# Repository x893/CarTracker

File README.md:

CarTracker
==========

CarTracker
STM32F10xCx, STM32F10xRx, STM32F205Rx, STM32F405Rx, STM32L1xxCx, STM32L1xxRx support.
Telit SL868 or SL869
Telit GL865 or GL868
CAN support,
MMA7455 accelerometer,
standard SIM or SIM On Chip
64 pins version can use battery, USB and RFM70 module (or other)

Shared PCB on OSH Park:

Cx version http://oshpark.com/shared_projects/hou07XOD

Rx version http://oshpark.com/shared_projects/wFTza6Pe

Cx version support direct connection GPS to GSM via wires (or change layout) so you can use buildin Python to implement tracker functions without STM32 MCU.

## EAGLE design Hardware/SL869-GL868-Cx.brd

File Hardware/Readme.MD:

Eagle Cadsoft
Case http://www.gainta.com/en/g431.html
See info for R9 value and R13

Shared PCB on OSH Park:

Cx version http://oshpark.com/shared_projects/hou07XOD
Rx version http://oshpark.com/shared_projects/wFTza6Pe

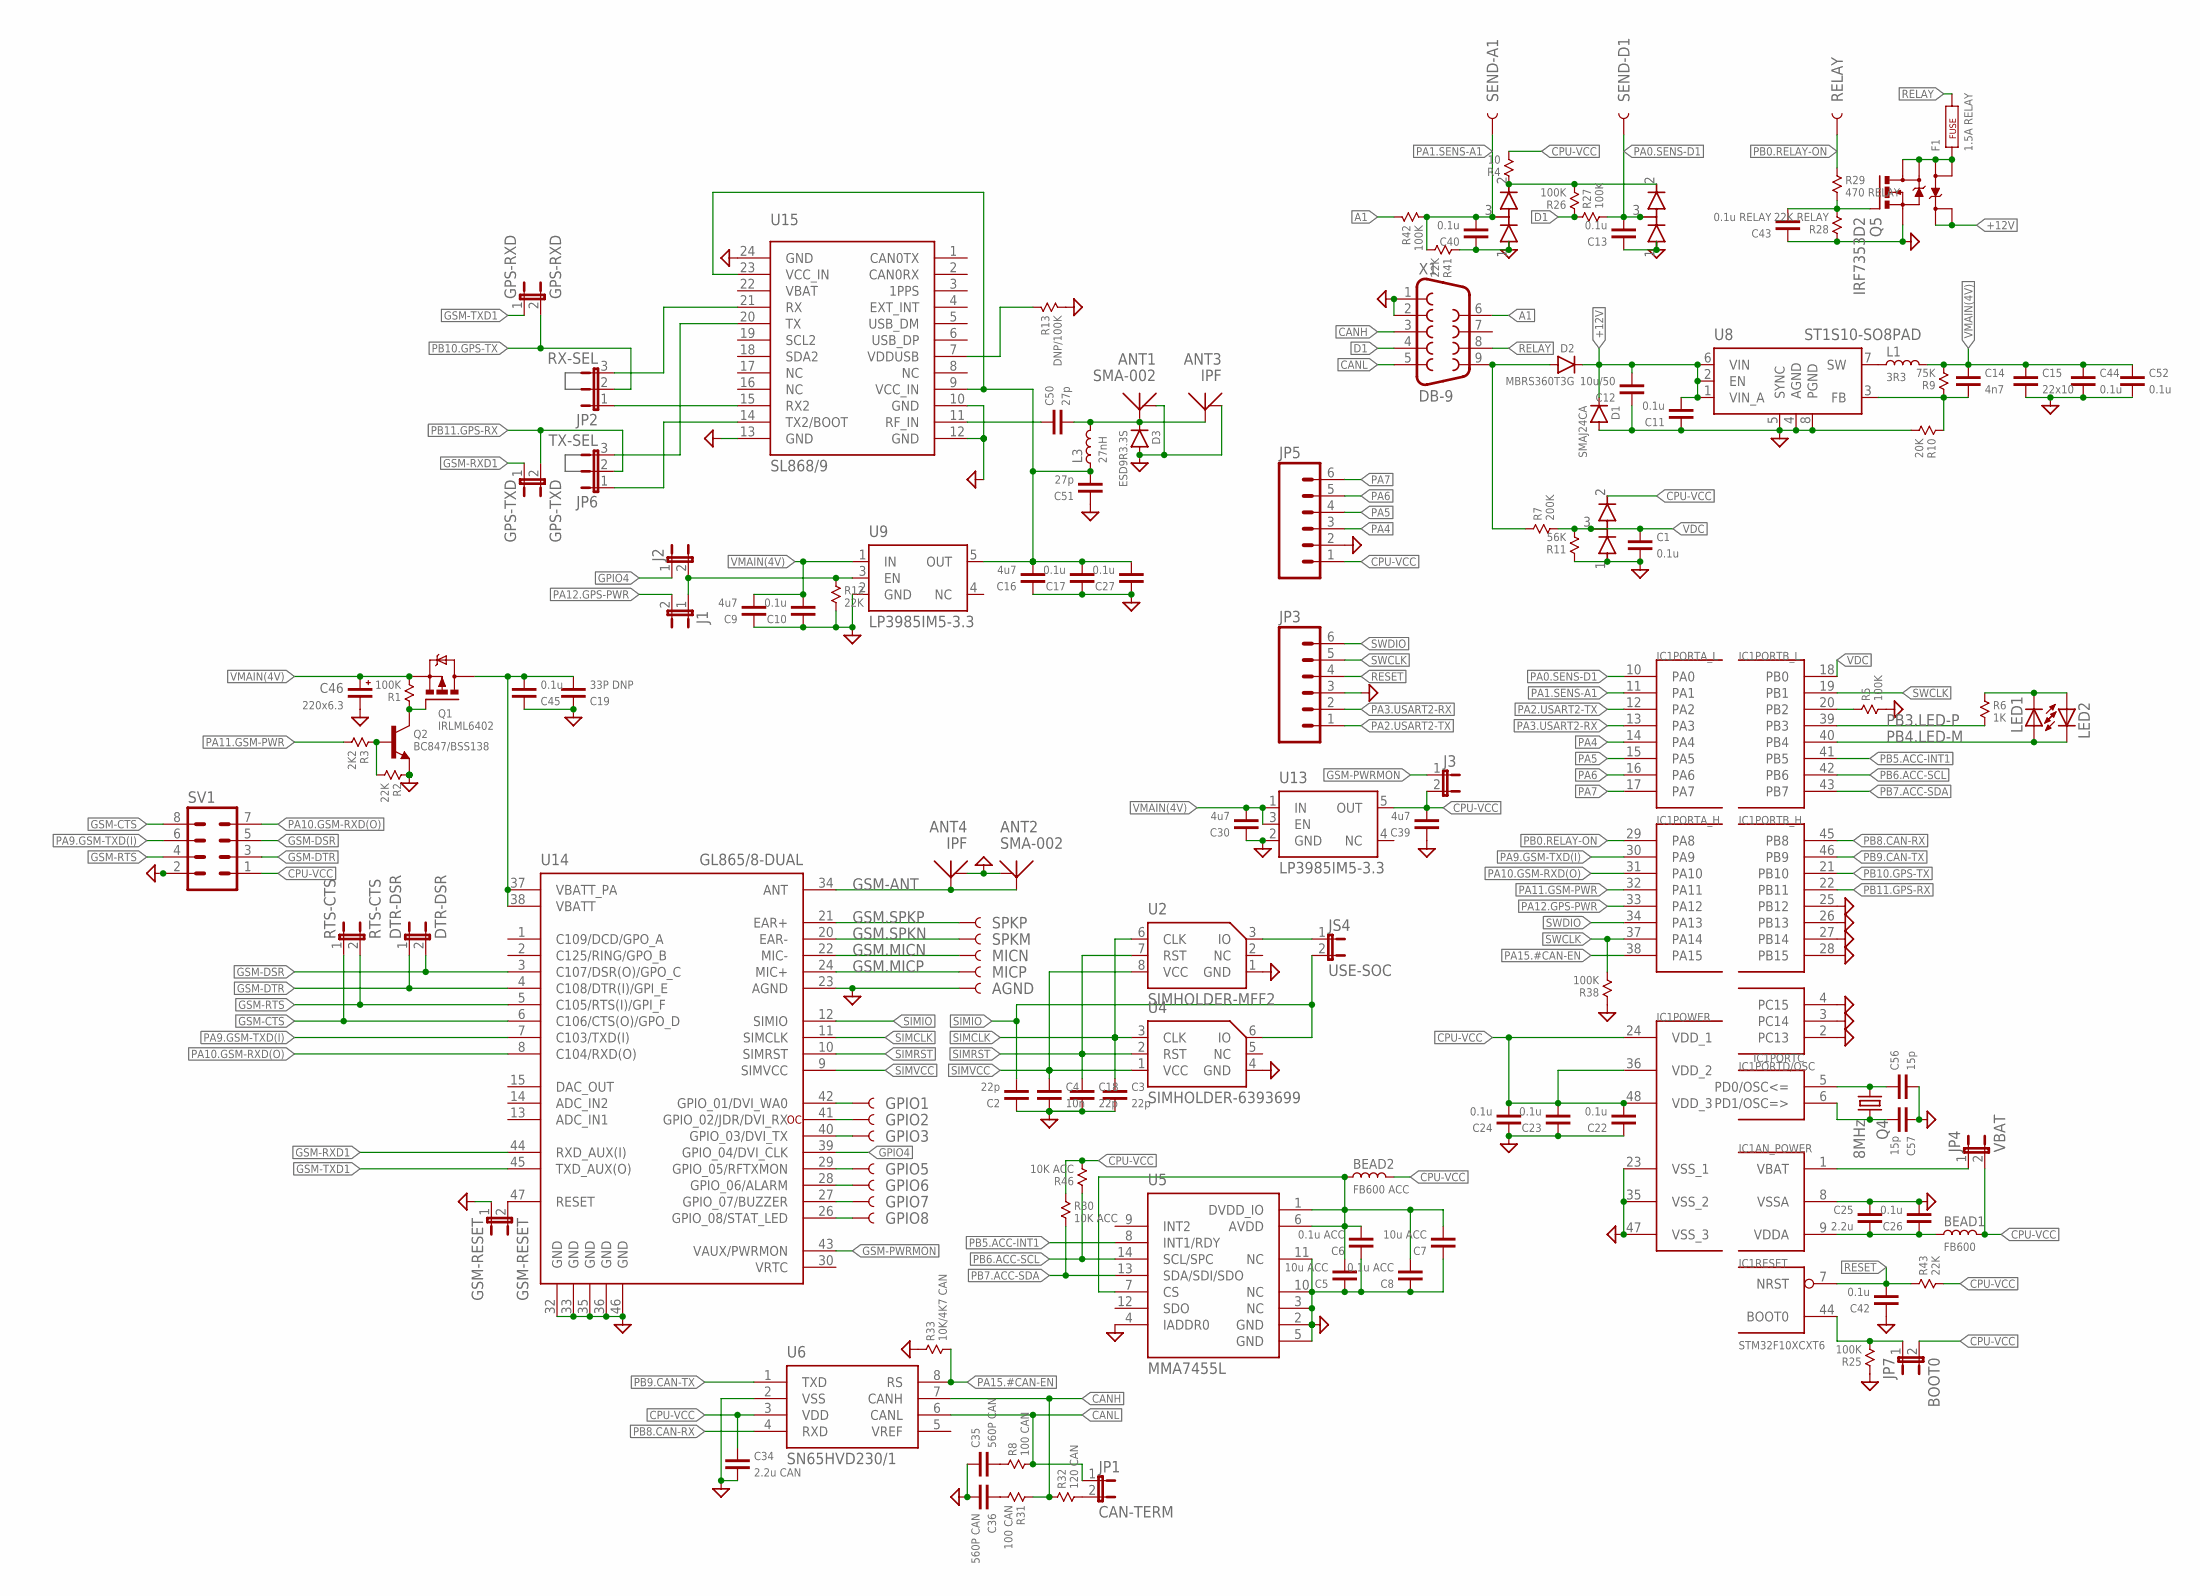
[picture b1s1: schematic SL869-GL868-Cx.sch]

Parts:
AGND: TEST-POINT1; PAD.1X1
ANT1, ANT2: SMA-002
ANT3, ANT4: IPF; MM9329
BEAD1: FB600; 0603
BEAD2: FB600 ACC; 0603
C1, C10, C11, C13, C17, C22, C23, C24, C26, C27, C40, C42, C44, C45, C52: 0.1u; 0603
C2, C3, C18: 22p; 0603
C4: 10n; 0603
C5, C7: 10u ACC; 0603
C6, C8: 0.1u ACC; 0603
C9, C16, C30, C39: 4u7; 0603
C12: 10u/50; 1206
C14: 4n7; 0603
C15: 22x10; 1206
C19: 33P DNP; 0603
C25: 2.2u; 0603
C34: 2.2u CAN; 0603
C35, C36: 560P CAN; 0603
C43: 0.1u RELAY; 0603
C46: 220x6.3; CT7343
C50, C51: 27p; 0603
C56, C57: 15p; 0603
D1: SMAJ24CA; SMA
D2: MBRS360T3G; SMC
D3: ESD9R3.3S; SOD-923
D4, D5, D14: BAV99; SOT-23
DTR-DSR: DTR-DSR; SJ_2S-NO
F1: 1.5A RELAY; 1812
GPIO1, GPIO2, GPIO3, GPIO5, GPIO6, GPIO7, GPIO8: TEST-POINT1; PAD.1X1
GPS-RXD: GPS-RXD; SJ_2S-NO
GPS-TXD: GPS-TXD; SJ_2S-NO
GSM-RESET: GSM-RESET; SJ_2S-NO
IC1: STM32F10XCXT6; TQFP48
J1, J2, J3: JUMPER-2SMD-NO; SJ_2S-NO
JP1: CAN-TERM; SJ_2S-NO
JP2: RX-SEL; SJ_3
JP3, JP5: M06SIP; 1X06
JP4: VBAT; SJ_2S-NO
JP6: TX-SEL; SJ_3
JP7: BOOT0; SJ_2S-NO
JS4: USE-SOC; SJ_2S-NO
L1: 3R3; CDRH6D38NP
L3: 27nH; 0603
LED1, LED2: LED3MM
MICN: TEST-POINT1; PAD.1X1
MICP: TEST-POINT1; PAD.1X1
Q1: IRLML6402; SOT-23
Q2: BC847/BSS138; SOT-23
Q4: 8MHz; HC49U-V
Q5: IRF7353D2; SO08
R1, R5, R25, R26, R27, R38, R42: 100K; 0603
R2, R12, R41, R43: 22K; 0603
R3: 2K2; 0603
R4: 10; 0603
R6: 1K; 0603
R7: 200K; 0603
R8, R31: 100 CAN; 0603
R9: 75K; 0603
R10: 20K; 0603
R11: 56K; 0603
R13: DNP/100K; 0603
R28: 22K RELAY; 0603
R29: 470 RELAY; 0603
R30, R46: 10K ACC; 0603
R32: 120 CAN; 0603
R33: 10K/4K7 CAN; 0603
RELAY: TEST-POINT1; PAD.1X1
RTS-CTS: RTS-CTS; SJ_2S-NO
SEND-A1: TEST-POINT1; PAD.1X1
SEND-D1: TEST-POINT1; PAD.1X1
SPKM: TEST-POINT1; PAD.1X1
SPKP: TEST-POINT1; PAD.1X1
SV1: MA04-2
U2: SIMHOLDER-MFF2; MFF2
U4: SIMHOLDER-6393699; 6393699-1
U5: MMA7455L; LGA14
U6: SN65HVD230/1; SO08
U8: ST1S10-SO8PAD; SO08-EPAD
U9, U13: LP3985IM5-3.3; SOT23-5
U14: GL865/8-DUAL
U15: SL868/9
X1: DB-9; DB9

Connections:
+12-IN: D2.P$2 (A), R7.1, X1.9
+12V: C11.1, C12.1, D1.P$1 (C), D2.P$1 (C), Q5.7 (K), Q5.8 (K), U8.1 (VIN_A), U8.2 (EN), U8.6 (VIN)
A1: R42.1, X1.6
ACC-VCC: BEAD2.1, C5.1, C6.1, C7.1, C8.1, U5.1 (DVDD_IO), U5.6 (AVDD), U5.7 (CS)
CANH: R31.1, R32.1, U6.7 (CANH), X1.3
CANL: JP1.1, R8.2, U6.6 (CANL), X1.5
CPU-VBAT: IC1.1 (VBAT), JP4.1
CPU-VCC: BEAD1.2, BEAD2.2, C22.1, C23.1, C24.1, C34.2, C39.1, D5.2 (+), IC1.24 (VDD_1), IC1.36 (VDD_2), IC1.48 (VDD_3), J3.2, JP4.2, JP5.1, JP7.2, R4.2, R30.1, R43.2, R46.2, SV1.1, U6.3 (VDD), U13.5 (OUT)
D1: R26.1, R27.1, X1.4
GND: AGND.P$1, ANT1.GND@1 (GND), ANT2.GND@1 (GND), ANT3.2 (GND), ANT4.2 (GND), C1.1, C2.2, C3.1, C4.1, C5.2, C6.2, C7.2, C8.2, C9.2, C10.2, C11.2, C12.2, C13.2, C15.1, C16.2, C17.2, C18.1, C19.2, C22.2, C23.2, C24.2, C25.2, C26.1, C27.2, C30.2, C34.1, C35.2, C36.1, C39.2, C40.2, C42.2, C43.2, C44.1, C45.2, C46.-, C51.2, C52.1, C56.1, C57.2, D1.P$2 (A), D3.2 (A), D4.1 (-), D5.1 (-), D14.1 (-), GSM-RESET.1, IC1.2 (PC13), IC1.3 (PC14), IC1.4 (PC15), IC1.8 (VSSA), IC1.23 (VSS_1), IC1.25 (PB12), IC1.26 (PB13), IC1.27 (PB14), IC1.28 (PB15), IC1.35 (VSS_2), IC1.47 (VSS_3), JP3.3, JP5.2, Q2.2 (E), Q5.3 (S), R2.1, R5.2, R10.2, R11.1, R12.2, R13.2, R25.1, R28.1, R33.1, R38.1, R41.1, SV1.2, U2.1 (GND), U4.4 (GND), U5.2 (GND), U5.3 (NC), U5.4 (IADDR0), U5.5 (GND), U5.10 (NC), U5.11 (NC), U6.2 (VSS), U8.4 (AGND), U8.5 (SYNC), U8.8 (PGND), U9.2 (GND), U13.2 (GND), U14.23 (AGND), U14.32 (GND), U14.33 (GND), U14.35 (GND), U14.36 (GND), U14.46 (GND), U15.10 (GND), U15.12 (GND), U15.13 (GND), U15.24 (GND), X1.1, X1.2
GPIO1: GPIO1.P$1, U14.42 (GPIO_01/DVI_WA0)
GPIO2: GPIO2.P$1, U14.41 (GPIO_02/JDR/DVI_RX)
GPIO3: GPIO3.P$1, U14.40 (GPIO_03/DVI_TX)
GPIO4: J2.1, U14.39 (GPIO_04/DVI_CLK)
GPIO5: GPIO5.P$1, U14.29 (GPIO_05/RFTXMON)
GPIO6: GPIO6.P$1, U14.28 (GPIO_06/ALARM)
GPIO7: GPIO7.P$1, U14.27 (GPIO_07/BUZZER)
GPIO8: GPIO8.P$1, U14.26 (GPIO_08/STAT_LED)
GPS-PWR: J1.1, J2.2, R12.1, U9.3 (EN)
GPS-RX0: JP2.1, U15.15 (RX2)
GPS-RX1: JP2.3, U15.21 (RX)
GPS-TX0: JP6.1, U15.14 (TX2/BOOT)
GPS-TX1: JP6.3, U15.20 (TX)
GPS-VCC: C16.1, C17.1, C27.1, C51.1, L3.1, U9.5 (OUT), U15.9 (VCC_IN), U15.23 (VCC_IN)
GSM-ANT: ANT2.A (ANT), ANT4.1 (ANT), U14.34 (ANT)
GSM-CTS: RTS-CTS.1, SV1.8, U14.6 (C106/CTS(O)/GPO_D)
GSM-DSR: DTR-DSR.2, SV1.5, U14.3 (C107/DSR(O)/GPO_C)
GSM-DTR: DTR-DSR.1, SV1.3, U14.4 (C108/DTR(I)/GPI_E)
GSM-PWRMON: J3.1, U14.43 (VAUX/PWRMON)
GSM-RESET: GSM-RESET.2, U14.47 (RESET)
GSM-RTS: RTS-CTS.2, SV1.4, U14.5 (C105/RTS(I)/GPI_F)
GSM-RXD1: GPS-TXD.1, U14.44 (RXD_AUX(I))
GSM-TXD1: GPS-RXD.1, U14.45 (TXD_AUX(O))
GSM-VCC: C19.1, C45.1, Q1.3 (D), U14.37 (VBATT_PA), U14.38 (VBATT)
GSM.MICN: MICN.P$1, U14.22 (MIC-)
GSM.MICP: MICP.P$1, U14.24 (MIC+)
GSM.SPKN: SPKM.P$1, U14.20 (EAR-)
GSM.SPKP: SPKP.P$1, U14.21 (EAR+)
unnamed: JP1.2, R32.2
unnamed: IC1.20 (PB2), R5.1
unnamed: F1.1, Q5.1 (A), Q5.2 (A), Q5.5 (D), Q5.6 (D)
unnamed: Q1.1 (G), Q2.3 (C), R1.1
unnamed: JS4.1, U2.3 (IO)
unnamed: C50.2, U15.11 (RF_IN)
unnamed: Q2.1 (B), R2.2, R3.1
unnamed: L1.P$1 (1), U8.7 (SW)
unnamed: C35.1, R8.1
unnamed: C36.2, R31.2
unnamed: R13.1, U15.7 (VDDUSB)
unnamed: LED1.K (C), LED2.A, R6.1
unnamed: C56.2, IC1.5 (PD0/OSC<=), Q4.1
unnamed: IC1.44 (BOOT0), JP7.1, R25.2
unnamed: C14.1, R9.1, R10.1, U8.3 (FB)
unnamed: C57.1, IC1.6 (PD1/OSC=>), Q4.2
unnamed: ANT1.A (ANT), ANT3.1 (ANT), C50.1, D3.1 (C), L3.2
unnamed: C43.1, Q5.4 (G), R28.2, R29.2
PA0.SENS-D1: C13.1, D4.3 (S), IC1.10 (PA0), R27.2, SEND-D1.P$1
PA1.SENS-A1: C40.1, D14.3 (S), IC1.11 (PA1), R41.2, R42.2, SEND-A1.P$1
PA2.USART2-TX: IC1.12 (PA2), JP3.1
PA3.USART2-RX: IC1.13 (PA3), JP3.2
PA4: IC1.14 (PA4), JP5.3
PA5: IC1.15 (PA5), JP5.4
PA6: IC1.16 (PA6), JP5.5
PA7: IC1.17 (PA7), JP5.6
PA9.GSM-TXD(I): IC1.30 (PA9), SV1.6, U14.7 (C103/TXD(I))
PA10.GSM-RXD(O): IC1.31 (PA10), SV1.7, U14.8 (C104/RXD(O))
PA11.GSM-PWR: IC1.32 (PA11), R3.2
PA12.GPS-PWR: IC1.33 (PA12), J1.2
PA15.#CAN-EN: IC1.38 (PA15), R33.2, U6.8 (RS)
PB0.RELAY-ON: IC1.29 (PA8), R29.1, RELAY.P$1
PB3.LED-P: IC1.39 (PB3), R6.2
PB4.LED-M: IC1.40 (PB4), LED1.A, LED2.K (C)
PB5.ACC-INT1: IC1.41 (PB5), U5.8 (INT1/RDY)
PB6.ACC-SCL: IC1.42 (PB6), R46.1, U5.14 (SCL/SPC)
PB7.ACC-SDA: IC1.43 (PB7), R30.2, U5.13 (SDA/SDI/SDO)
PB8.CAN-RX: IC1.45 (PB8), U6.4 (RXD)
PB9.CAN-TX: IC1.46 (PB9), U6.1 (TXD)
PB10.GPS-TX: GPS-RXD.2, IC1.21 (PB10), JP2.2
PB11.GPS-RX: GPS-TXD.2, IC1.22 (PB11), JP6.2
RELAY: F1.2, X1.8
RESET: C42.1, IC1.7 (NRST), JP3.4, R43.1
SENS-VCC: D4.2 (+), D14.2 (+), R4.1, R26.2
SIMCLK: C3.2, U2.6 (CLK), U4.3 (CLK), U14.11 (SIMCLK)
SIMIO: C2.1, JS4.2, U4.6 (IO), U14.12 (SIMIO)
SIMRST: C18.2, U2.7 (RST), U4.2 (RST), U14.10 (SIMRST)
SIMVCC: C4.2, U2.8 (VCC), U4.1 (VCC), U14.9 (SIMVCC)
SWCLK: IC1.19 (PB1), IC1.37 (PA14), JP3.5, R38.2
SWDIO: IC1.34 (PA13), JP3.6
VDC: C1.2, D5.3 (S), IC1.18 (PB0), R7.2, R11.2
VDDA: BEAD1.1, C25.1, C26.2, IC1.9 (VDDA)
VMAIN(4V): C9.1, C10.1, C14.2, C15.2, C30.1, C44.2, C46.+, C52.2, L1.P$2 (2), Q1.2 (S), R1.2, R9.2, U9.1 (IN), U13.1 (IN), U13.3 (EN)

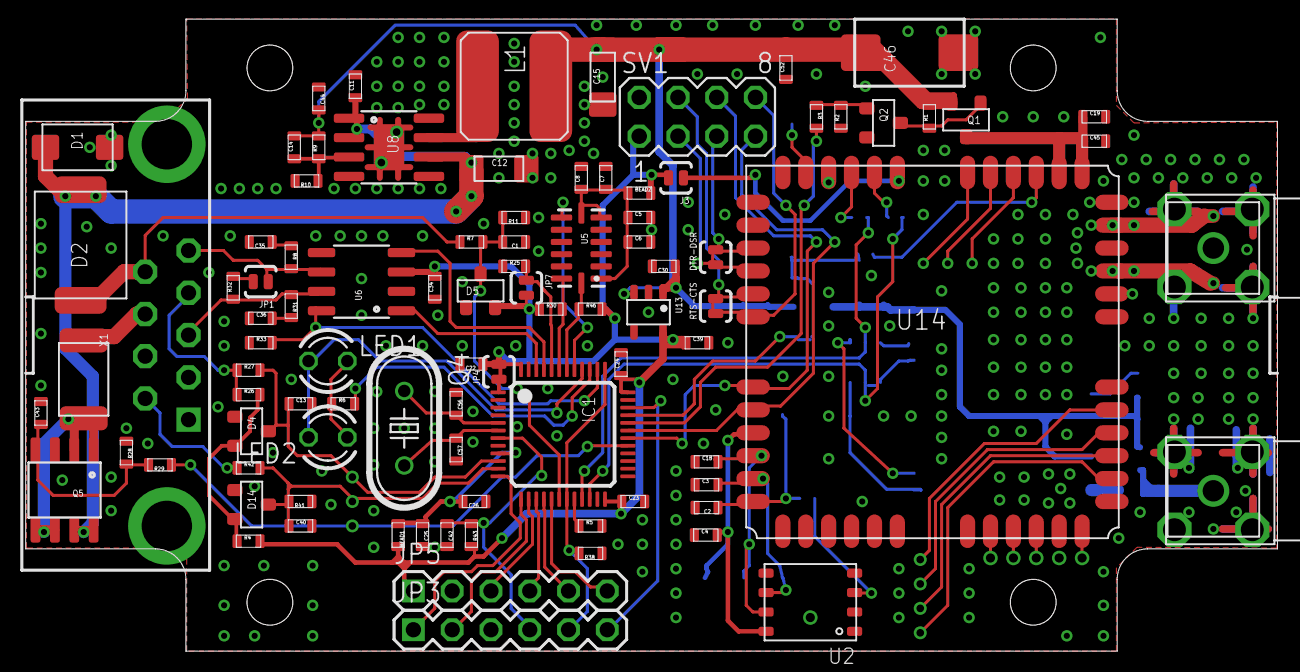
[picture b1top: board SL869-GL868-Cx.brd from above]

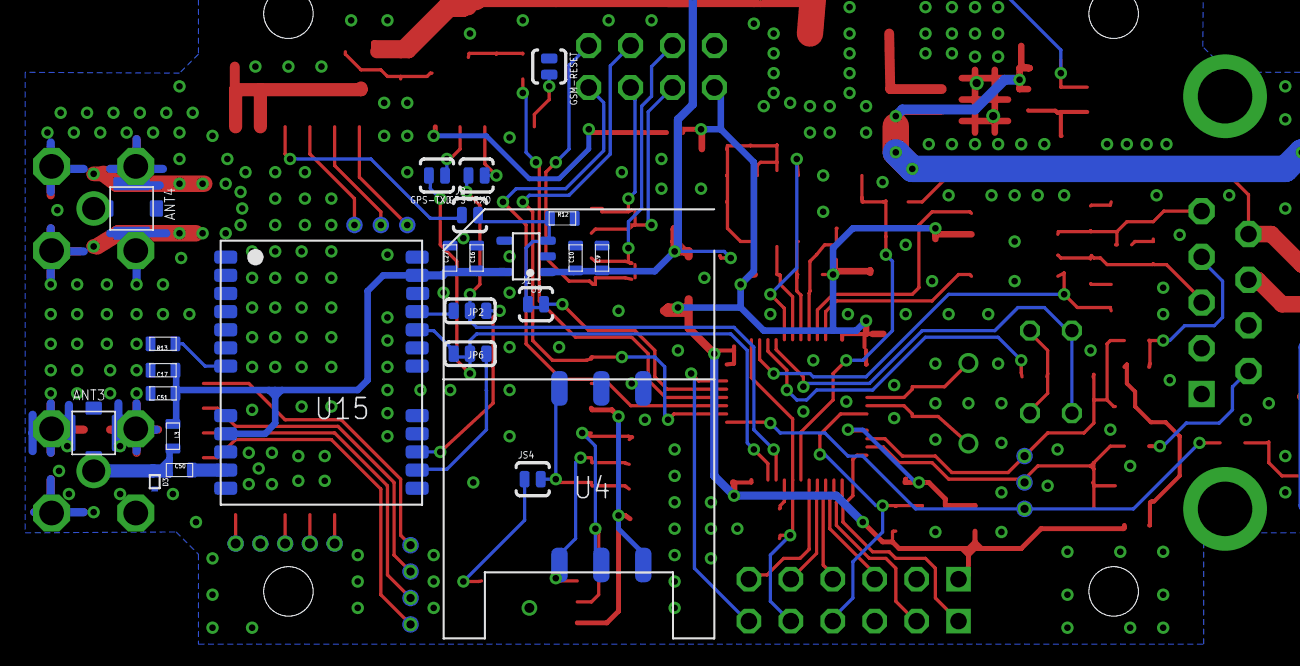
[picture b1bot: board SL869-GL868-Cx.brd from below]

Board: 2 copper layers, 133 parts (39 on the bottom side), 91 nets.

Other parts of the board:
U$1: G403

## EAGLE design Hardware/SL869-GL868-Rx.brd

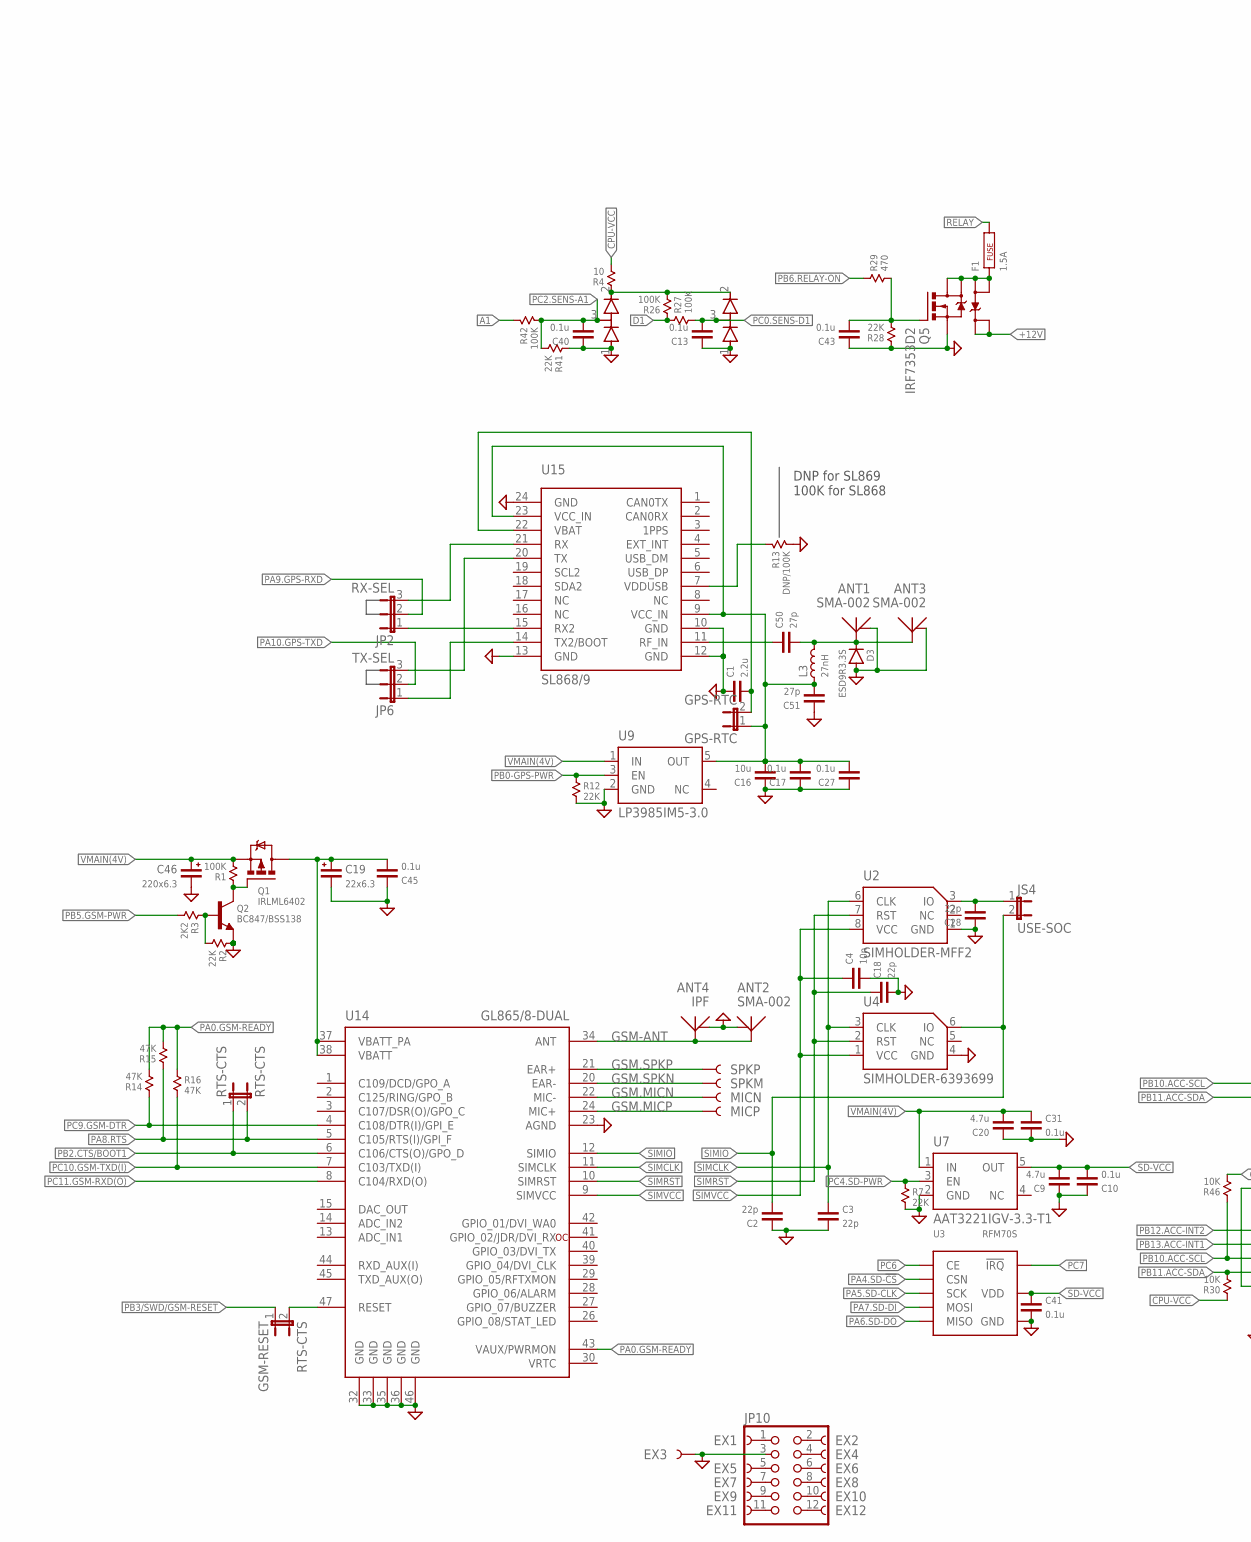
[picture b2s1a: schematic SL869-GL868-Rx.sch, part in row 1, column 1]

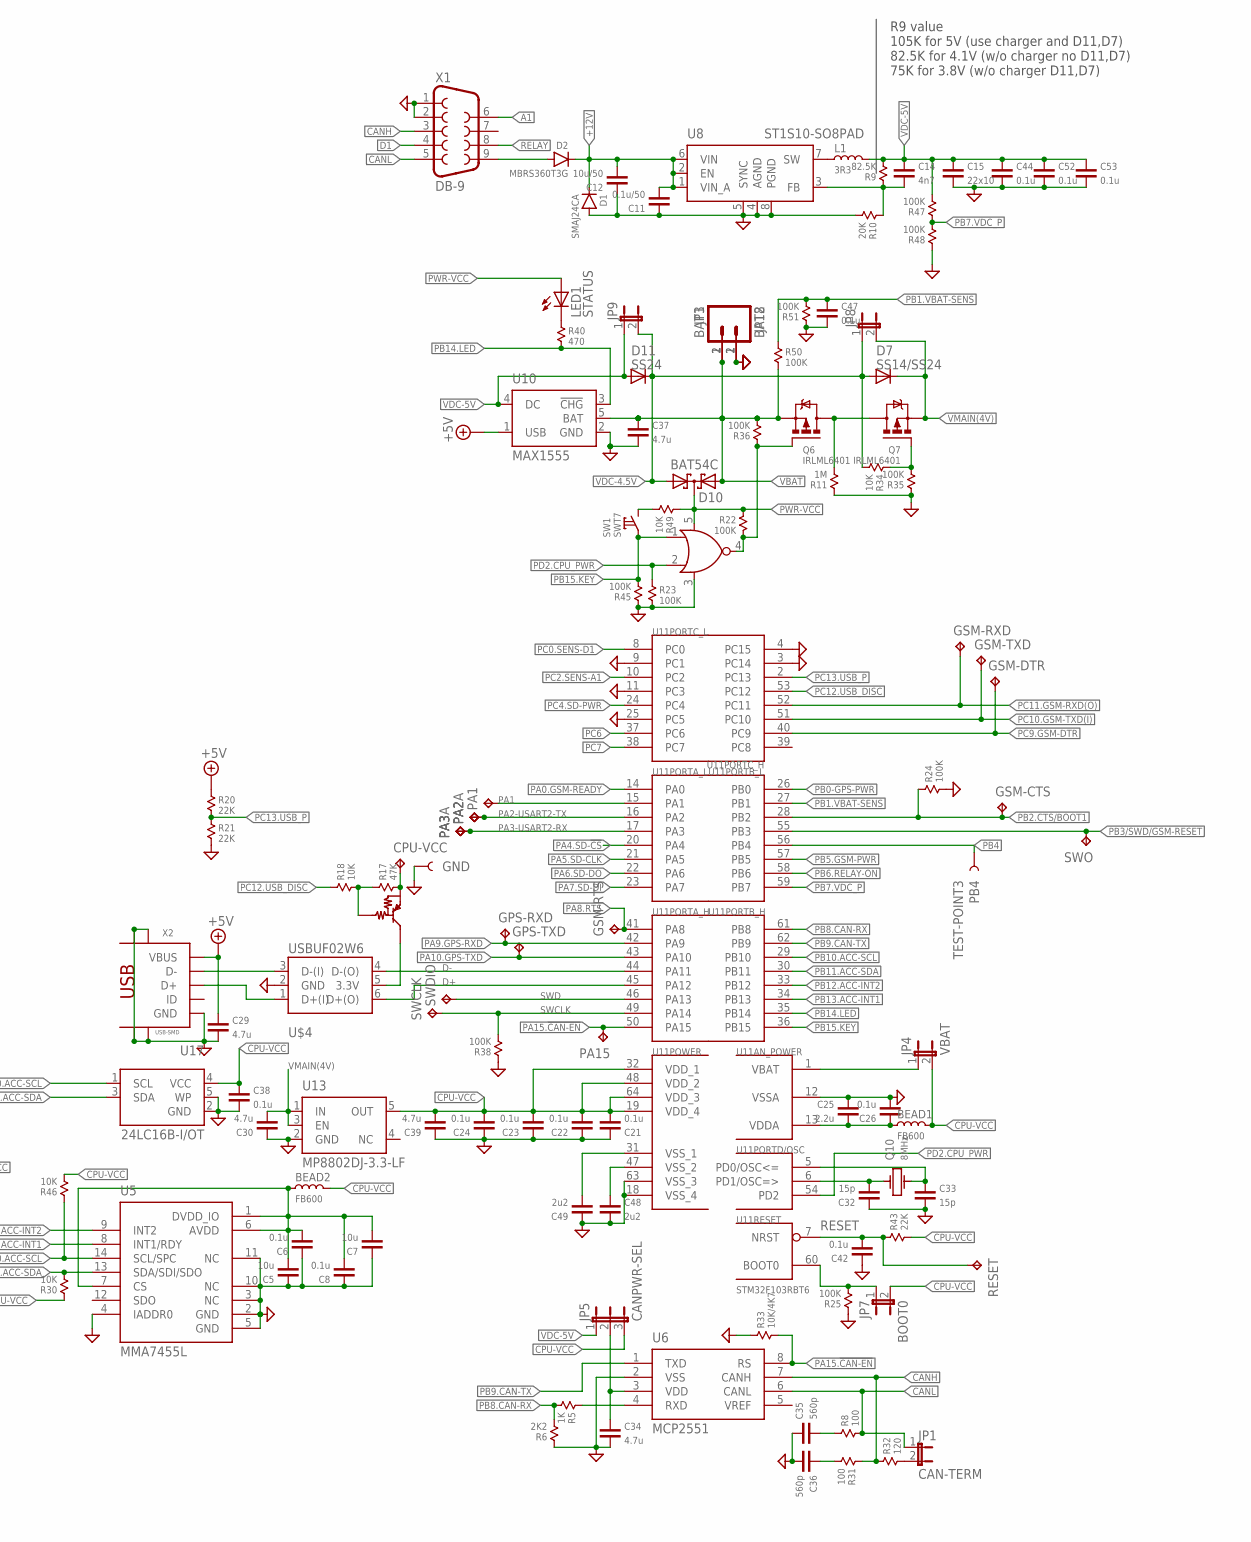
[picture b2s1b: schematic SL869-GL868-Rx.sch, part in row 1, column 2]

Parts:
ANT1, ANT2: SMA-002
ANT3: SMA-002; MM9329
ANT4: IPF; MM9329
BEAD1, BEAD2: FB600; 0603
C1, C25: 2.2u; 0603
C2, C3, C18, C28: 22p; 0603
C4: 10n; 0603
C5, C7, C16: 10u; 0603
C6, C8, C10, C13, C17, C21, C22, C23, C24, C26, C27, C31, C38, C40, C41, C42, C43, C44, C45, C47, C52, C53: 0.1u; 0603
C9, C20, C29, C30, C34, C37, C39: 4.7u; 0603
C11: 0.1u/50; 0603
C12: 10u/50; 1206
C14: 4n7; 0603
C15: 22x10; 1206
C19: 22x6.3; CT3528
C32, C33: 15p; 0603
C35, C36: 560p; 0603
C46: 220x6.3; CT7343
C48, C49: 2u2; 0603
C50, C51: 27p; 0603
CPU-VCC: TPTP09R; TP09R
D1: SMAJ24CA; SMA
D2: MBRS360T3G; SMC
D3: ESD9R3.3S; SOD-923
D4, D14: BAV99; SOT-23
D7: SS14/SS24; SMA-DIODE
D10: BAT54C; SOT23
D11: SS24; SMA-DIODE
EX1, EX2, EX3, EX4, EX5, EX6, EX7, EX8, EX9, EX10, EX11, EX12: TEST-POINT1; PAD.1X1
F1: 1.5A; 1812
GND: TEST-POINT3; PAD.03X.03
GPS-RTC: GPS-RTC; SJ_2S-NO
GPS-RXD: TPTP07R; TP07R
GPS-TXD: TPTP07R; TP07R
GSM-CTS: TPTP07R; TP07R
GSM-DTR: TPTP07R; TP07R
GSM-RESET: RTS-CTS; SJ_2S-NO
GSM-RTS: TPTP07R; TP07R
GSM-RXD: TPTP07R; TP07R
GSM-TXD: TPTP07R; TP07R
JP1: CAN-TERM; SJ_2S-NO
JP2: RX-SEL; SJ_3
JP3: BAT2; S2B-PH
JP4: VBAT; SJ_2S-NO
JP5: CANPWR-SEL; SJ_3
JP6: TX-SEL; SJ_3
JP7: BOOT0; SJ_2S-NO
JP8, JP9: JUMPER-2SMD-NO; SJ_2S-NO
JP10: PINHD-2X6; 2X06
JP18: BAT1; CI1102M1H
JS4: USE-SOC; SJ_2S-NO
L1: 3R3; CDRH6D38NP
L3: 27nH; 0603
LED1: STATUS; LED3MM
MICN: TEST-POINT1; PAD.1X1
MICP: TEST-POINT1; PAD.1X1
PA1, PA2, PA3: TPTP08R; TP08R
PA2A, PA3A, PA15: TPTP07R; TP07R
PB4: TEST-POINT3; PAD.03X.03
Q1: IRLML6402; SOT-23
Q2: BC847/BSS138; SOT-23
Q5: IRF7353D2; SO08
Q6, Q7: IRLML6401; SOT-23
Q10: 8MHz; KX-9A
R1, R22, R23, R24, R25, R26, R27, R35, R36, R38, R42, R45, R47, R48, R50, R51: 100K; 0603
R2, R7, R12, R20, R21, R28, R41, R43: 22K; 0603
R3, R6: 2K2; 0603
R4: 10; 0603
R5: 1K; 0603
R8, R31: 100; 0603
R9: 82.5K; 0603
R10: 20K; 0603
R11: 1M; 0603
R13: DNP/100K; 0603
R14, R15, R16, R17: 47K; 0603
R18, R30, R34, R46, R49: 10K; 0603
R29, R40: 470; 0603
R32: 120; 0603
R33: 10K/4K7; 0603
RESET: TPTP09R; TP09R
RTS-CTS: RTS-CTS; SJ_2S-NO
SPKM: TEST-POINT1; PAD.1X1
SPKP: TEST-POINT1; PAD.1X1
SW1: SWT7; SWT-7
SWCLK: TPTP09R; TP09R
SWDIO: TPTP09R; TP09R
SWO: TPTP07R; TP07R
U1: 74LVC1G02GV; SOT-753
U2: SIMHOLDER-MFF2; MFF2
U3: RFM70S
U4: SIMHOLDER-6393699; 6393699-1
U5: MMA7455L; LGA14
U6: MCP2551; SO08
U7: AAT3221IGV-3.3-T1; SOT23-5
U8: ST1S10-SO8PAD; SO08-EPAD
U9: LP3985IM5-3.0; SOT23-5
U10: MAX1555; SOT23-5
U11: STM32F103RBT6; TQFP64
U13: MP8802DJ-3.3-LF; SOT23-5
U14: GL865/8-DUAL
U15: SL868/9
U17: 24LC16B-I/OT; SOT23-5
U$3: PDTA114ET; SOT-23
U$4: USBUF02W6; SOT323-6
X1: DB-9; DB9
X2: USB-SMD; USB-MINIB

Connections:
+5V: C29.2, R20.1, U10.1 (USB), X2.VBUS
+12-IN: D2.P$2 (A), X1.9
+12V: C11.1, C12.1, D1.P$1 (C), D2.P$1 (C), Q5.7 (K), Q5.8 (K), U8.1 (VIN_A), U8.2 (EN), U8.6 (VIN)
A1: R42.1, X1.6
ACC-VCC: BEAD2.1, C5.1, C6.1, C7.1, C8.1, U5.1 (DVDD_IO), U5.6 (AVDD), U5.7 (CS)
CANH: R31.1, R32.1, U6.7 (CANH), X1.3
CANL: JP1.1, R8.2, U6.6 (CANL), X1.5
CPU-VBAT: JP4.1, U11.1 (VBAT)
CPU-VCC: BEAD1.2, BEAD2.2, C21.1, C22.1, C23.1, C24.1, C38.2, C39.1, CPU-VCC.TP, JP4.2, JP5.3, JP7.2, R4.2, R17.2, R30.1, R43.2, R46.2, U11.19 (VDD_4), U11.32 (VDD_1), U11.48 (VDD_2), U11.64 (VDD_3), U13.5 (OUT), U17.4 (VCC), U$3.2
D1: R26.1, R27.1, X1.4
D+: U11.45 (PA12), U$4.6 (D+(O))
D-: U11.44 (PA11), U$4.4 (D-(O))
GND: ANT1.GND@1 (GND), ANT2.GND@1 (GND), ANT3.2 (GND), ANT4.2 (GND), C1.2, C2.2, C3.1, C4.1, C5.2, C6.2, C7.2, C8.2, C9.2, C10.2, C11.2, C12.2, C13.2, C15.1, C16.2, C17.2, C18.1, C19.-, C20.2, C21.2, C22.2, C23.2, C24.2, C25.2, C26.1, C27.2, C28.2, C29.1, C30.2, C31.1, C32.2, C33.1, C34.1, C35.2, C36.1, C37.1, C38.1, C39.2, C40.2, C41.1, C42.2, C43.2, C44.1, C45.2, C46.-, C47.1, C48.1, C49.2, C51.2, C52.1, C53.1, D1.P$2 (A), D3.2 (A), D4.1 (-), D14.1 (-), EX3.P$1, GND.P$1, JP3.1, JP10.3, JP18.2, Q2.2 (E), Q5.3 (S), R2.1, R6.1, R7.2, R10.2, R11.1, R12.2, R13.2, R21.2, R23.2, R24.2, R25.1, R28.1, R33.1, R35.1, R38.1, R41.1, R45.1, R48.1, R51.1, U1.3 (GND), U2.1 (GND), U3.GND, U4.4 (GND), U5.2 (GND), U5.3 (NC), U5.4 (IADDR0), U5.5 (GND), U5.10 (NC), U5.11 (NC), U6.2 (VSS), U7.2 (GND), U8.4 (AGND), U8.5 (SYNC), U8.8 (PGND), U9.2 (GND), U10.2 (GND), U11.3 (PC14), U11.4 (PC15), U11.9 (PC1), U11.11 (PC3), U11.12 (VSSA), U11.18 (VSS_4), U11.25 (PC5), U11.63 (VSS_3), U13.2 (GND), U14.23 (AGND), U14.32 (GND), U14.33 (GND), U14.35 (GND), U14.36 (GND), U14.46 (GND), U15.10 (GND), U15.12 (GND), U15.13 (GND), U15.24 (GND), U17.2 (GND), U17.5 (WP), U$4.2 (GND), X1.1, X1.2, X2.GND, X2.GND@1 (GND), X2.GND@2 (GND), X2.GND@3 (GND), X2.GND@4 (GND)
GPS-RX0: JP2.1, U15.15 (RX2)
GPS-RX1: JP2.3, U15.21 (RX)
GPS-TX0: JP6.1, U15.14 (TX2/BOOT)
GPS-TX1: JP6.3, U15.20 (TX)
GPS-VCC: C16.1, C17.1, C27.1, C51.1, GPS-RTC.1, L3.1, U9.5 (OUT), U15.9 (VCC_IN), U15.23 (VCC_IN)
GSM-ANT: ANT2.A (ANT), ANT4.1 (ANT), U14.34 (ANT)
GSM-RESET: GSM-RESET.2, U14.47 (RESET)
GSM-VCC: C19.+, C45.1, Q1.3 (D), U14.37 (VBATT_PA), U14.38 (VBATT)
GSM.MICN: MICN.P$1, U14.22 (MIC-)
GSM.MICP: MICP.P$1, U14.24 (MIC+)
GSM.SPKN: SPKM.P$1, U14.20 (EAR-)
GSM.SPKP: SPKP.P$1, U14.21 (EAR+)
unnamed: JP1.2, R32.2
unnamed: U$3.3, U$4.5 (3.3V)
unnamed: C1.1, GPS-RTC.2, U15.22 (VBAT)
unnamed: Q7.1 (G), R34.1, R35.2
unnamed: F1.1, Q5.1 (A), Q5.2 (A), Q5.5 (D), Q5.6 (D)
unnamed: Q1.1 (G), Q2.3 (C), R1.1
unnamed: C49.1, U11.31 (VSS_1)
unnamed: C48.2, U11.47 (VSS_2)
unnamed: C28.1, JS4.1, U2.3 (IO)
unnamed: C50.2, U15.11 (RF_IN)
unnamed: Q2.1 (B), R2.2, R3.1
unnamed: L1.P$1 (1), U8.7 (SW)
unnamed: C35.1, R8.1
unnamed: C36.2, R31.2
unnamed: R13.1, U15.7 (VDDUSB)
unnamed: LED1.K (C), R40.1
unnamed: R5.1, U6.4 (RXD)
unnamed: C34.2, JP5.2, U6.3 (VDD)
unnamed: EX1.P$1, JP10.1
unnamed: EX2.P$1, JP10.2
unnamed: EX4.P$1, JP10.4
unnamed: C32.1, Q10.1, U11.6 (PD1/OSC=>)
unnamed: EX5.P$1, JP10.5
unnamed: JP7.1, R25.2, U11.60 (BOOT0)
unnamed: C14.1, R9.1, R10.1, U8.3 (FB)
unnamed: EX6.P$1, JP10.6
unnamed: EX7.P$1, JP10.7
unnamed: EX8.P$1, JP10.8
unnamed: EX9.P$1, JP10.9
unnamed: EX10.P$1, JP10.10
unnamed: ANT1.A (ANT), ANT3.1 (ANT), C50.1, D3.1 (C), L3.2
unnamed: EX11.P$1, JP10.11
unnamed: EX12.P$1, JP10.12
unnamed: R49.2, SW1.2
unnamed: Q6.3 (D), Q7.3 (D), R11.2
unnamed: C43.1, Q5.4 (G), R28.2, R29.2
unnamed: U$4.3 (D-(I)), X2.D-
unnamed: U$4.1 (D+(I)), X2.D+
unnamed: C33.2, Q10.3 (2), U11.5 (PD0/OSC<=)
unnamed: R17.1, R18.2, U$3.1
PA0.GSM-READY: R14.2, R15.2, R16.1, U11.14 (PA0), U14.43 (VAUX/PWRMON)
PA1: PA1.TP, U11.15 (PA1)
PA2-USART2-TX: PA2.TP, PA2A.TP, U11.16 (PA2)
PA3-USART2-RX: PA3.TP, PA3A.TP, U11.17 (PA3)
PA4.SD-!CS: U3.CSN, U11.20 (PA4)
PA5.SD-CLK: U3.SCK, U11.21 (PA5)
PA6.SD-DO: U3.MISO, U11.22 (PA6)
PA7.SD-DI: U3.MOSI, U11.23 (PA7)
PA8.RTS: GSM-RTS.TP, R15.1, RTS-CTS.2, U11.41 (PA8), U14.5 (C105/RTS(I)/GPI_F)
PA9.GPS-RXD: GPS-RXD.TP, JP2.2, U11.42 (PA9)
PA10.GPS-TXD: GPS-TXD.TP, JP6.2, U11.43 (PA10)
PA15.!CAN-EN: PA15.TP, R33.2, U6.8 (RS), U11.50 (PA15)
PB0-GPS-PWR: R12.1, U9.3 (EN), U11.26 (PB0)
PB1.VBAT-SENS: C47.2, R50.1, R51.2, U11.27 (PB1)
PB2.CTS/BOOT1: GSM-CTS.TP, R24.1, RTS-CTS.1, U11.28 (PB2), U14.6 (C106/CTS(O)/GPO_D)
PB3/SWD/GSM-RESET: GSM-RESET.1, SWO.TP, U11.55 (PB3)
PB4: PB4.P$1, U11.56 (PB4)
PB5.GSM-PWR: R3.2, U11.57 (PB5)
PB6.RELAY-ON: R29.1, U11.58 (PB6)
PB7.VDC_P: R47.1, R48.2, U11.59 (PB7)
PB8.CAN-RX: R5.2, R6.2, U11.61 (PB8)
PB9.CAN-TX: U6.1 (TXD), U11.62 (PB9)
PB10.ACC-SCL: R46.1, U5.14 (SCL/SPC), U11.29 (PB10), U17.1 (SCL)
PB11.ACC-SDA: R30.2, U5.13 (SDA/SDI/SDO), U11.30 (PB11), U17.3 (SDA)
PB12.ACC-INT2: U5.9 (INT2), U11.33 (PB12)
PB13.ACC-INT1: U5.8 (INT1/RDY), U11.34 (PB13)
PB14.LED: R40.2, U10.3 (!CHG), U11.35 (PB14)
PB15.KEY: R45.2, SW1.1, U1.1 (A), U11.36 (PB15)
PC0.SENS-D1: C13.1, D4.3 (S), R27.2, U11.8 (PC0)
PC2.SENS-A1: C40.1, D14.3 (S), R41.2, R42.2, U11.10 (PC2)
PC4.SD-PWR: R7.1, U7.3 (EN), U11.24 (PC4)
PC6: U3.CE, U11.37 (PC6)
PC7: U3.IRQ (!IRQ), U11.38 (PC7)
PC9.GSM-DTR: GSM-DTR.TP, R14.1, U11.40 (PC9), U14.4 (C108/DTR(I)/GPI_E)
PC10.GSM-TXD(I): GSM-TXD.TP, R16.2, U11.51 (PC10), U14.7 (C103/TXD(I))
PC11.GSM-RXD(O): GSM-RXD.TP, U11.52 (PC11), U14.8 (C104/RXD(O))
PC12.USB_DISC: R18.1, U11.53 (PC12)
PC13.USB_P: R20.2, R21.1, U11.2 (PC13)
PD2.CPU_PWR: R23.1, U1.2 (B), U11.54 (PD2)
PWR-VCC: D10.3 (CC), LED1.A, R22.1, R49.1, U1.5 (VCC)
RELAY: F1.2, X1.8
RESET: C42.1, R43.1, RESET.TP, U11.7 (NRST)
SD-VCC: C9.1, C10.1, C41.2, U3.VDD, U7.5 (OUT)
SENS-VCC: D4.2 (+), D14.2 (+), R4.1, R26.2
SIMCLK: C3.2, U2.6 (CLK), U4.3 (CLK), U14.11 (SIMCLK)
SIMIO: C2.1, JS4.2, U4.6 (IO), U14.12 (SIMIO)
SIMRST: C18.2, U2.7 (RST), U4.2 (RST), U14.10 (SIMRST)
SIMVCC: C4.2, U2.8 (VCC), U4.1 (VCC), U14.9 (SIMVCC)
SWCLK: R38.2, SWCLK.TP, U11.49 (PA14)
SWD: SWDIO.TP, U11.46 (PA13)
VBAT: C37.2, D10.2 (A2), JP3.2, JP18.1, Q6.2 (S), R36.2, R50.2, U10.5 (BAT)
VDC-4.5V: D7.A, D10.1 (A1), D11.C, JP8.1, JP9.2, R34.2
VDC-5V: C14.2, C15.2, C44.2, C52.2, C53.2, D11.A, JP5.1, JP9.1, L1.P$2 (2), R9.2, R47.2, U10.4 (DC)
VDDA: BEAD1.1, C25.1, C26.2, U11.13 (VDDA)
VE: Q6.1 (G), R22.2, R36.1, U1.4 (Y)
VMAIN(4V): C20.1, C30.1, C31.2, C46.+, D7.C, JP8.2, Q1.2 (S), Q7.2 (S), R1.2, U7.1 (IN), U9.1 (IN), U13.1 (IN), U13.3 (EN)

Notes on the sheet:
R9 value 105K for 5V (use charger and D11,D7) 82.5K for 4.1V (w/o charger no D11,D7) 75K for 3.8V (w/o charger D11,D7)
DNP for SL869 100K for SL868

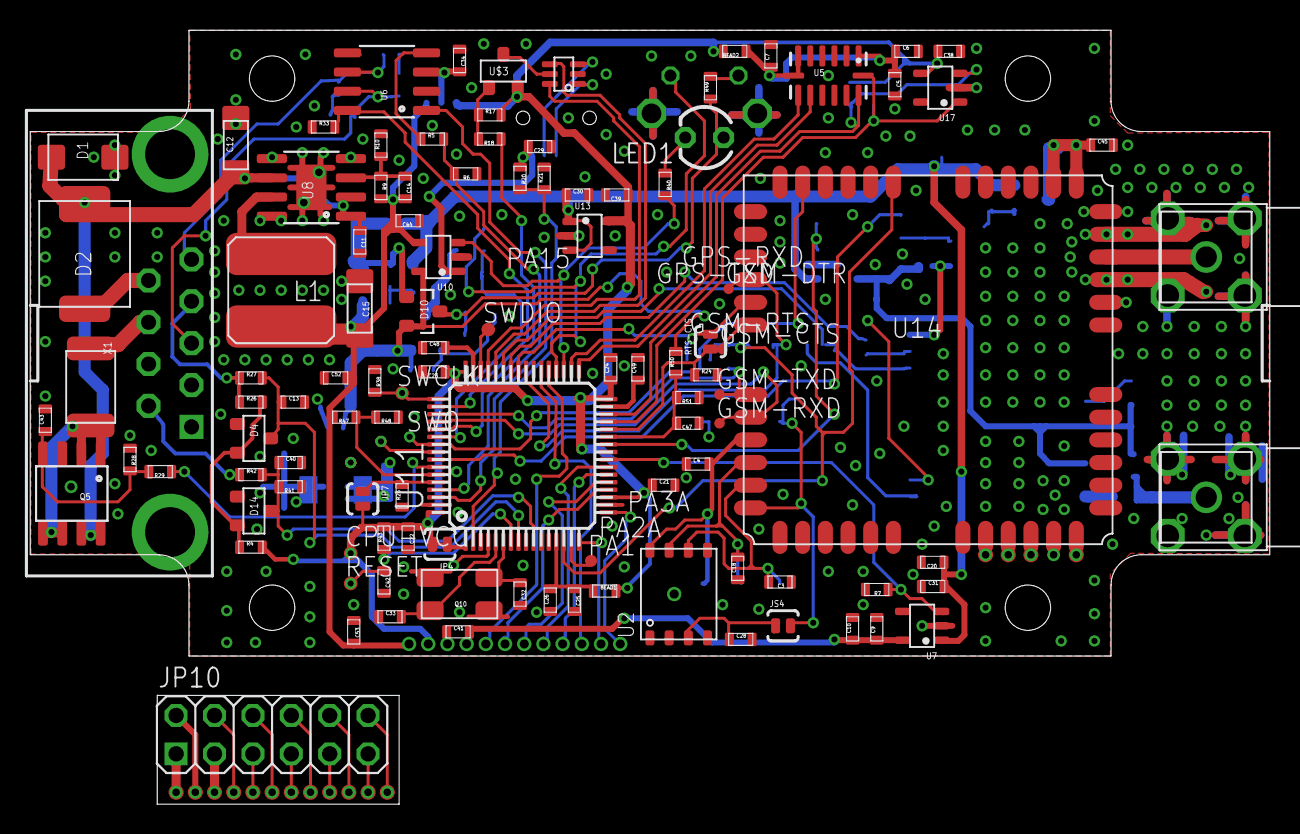
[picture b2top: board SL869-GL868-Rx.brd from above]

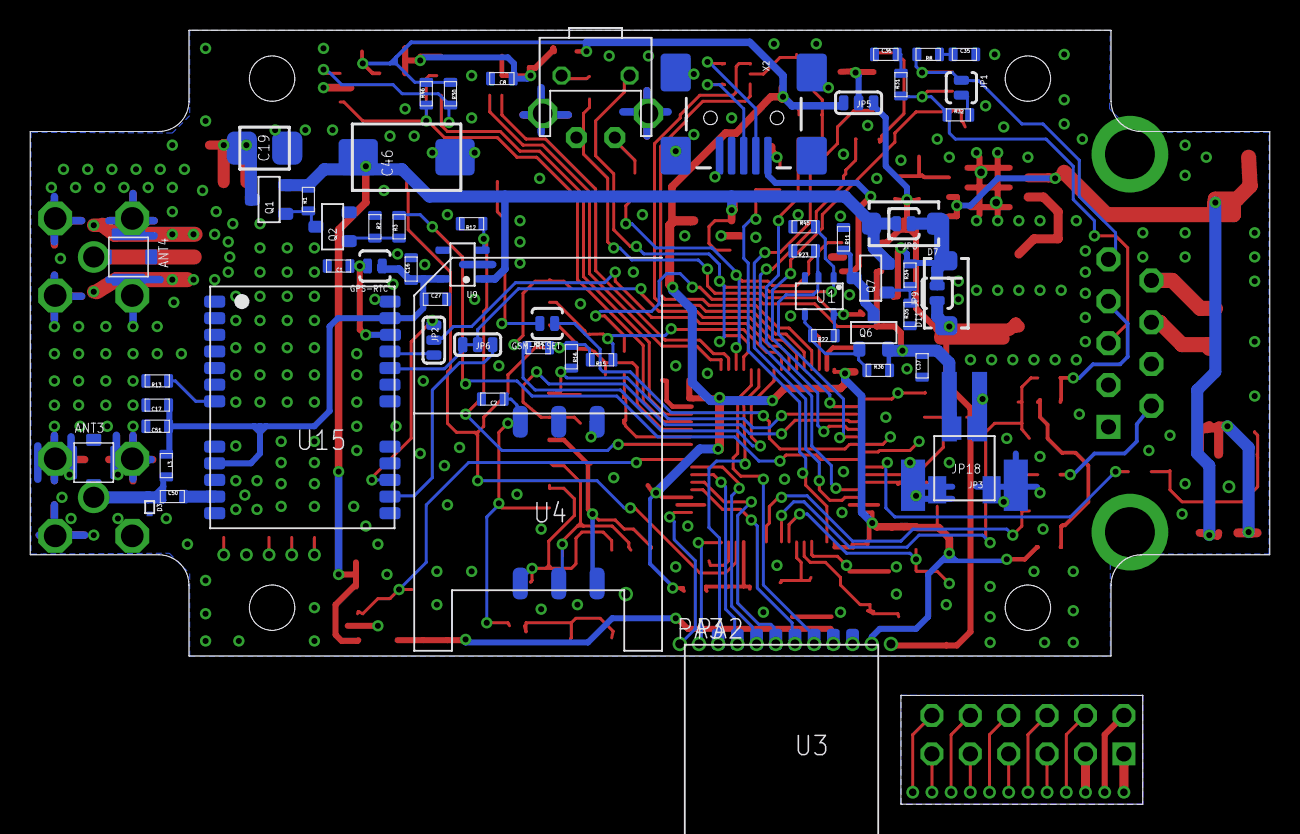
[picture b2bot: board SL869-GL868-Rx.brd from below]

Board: 2 copper layers, 82.0 x 41.4 mm, 196 parts (62 on the bottom side), 121 nets.

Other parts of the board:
U$1: G403

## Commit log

2014-03-02 Commit firmware for STM32F10xCx (48 pins) and STM32F10xRx (64 pins)
2014-03-24 Add remark for R9 and R13 values
2014-03-24 Add X893 library
2014-03-24 Add datasheets
2014-04-25 Add links to OSH Park
2014-04-25 Cosmetic changes
2014-04-25 Fix error with OSH Park DRU file
2014-04-26 Add to Readme.md about Cx version w/o STM32 MCU
2014-05-03 Change to FreeRTOS 8.0.1
2014-06-07 Fix schematic/layout
2014-06-27 Update Eagle library
2014-12-25 Fix error with LED on PB3/PB4 with Cx version
2015-02-07 Fox for RX (64 pin CPU) version
2015-02-11 Fix CTS pin initialization
2015-02-21 Add AT#SKIPESC for Telit GL86x
2024-02-24 Update gps.c - fix copy-pasted code
